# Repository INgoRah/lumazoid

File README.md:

# Lumazoid

Firmware for the Lumazoid realtime music visualizer board from nootropic design.
Detailed technical information about Lumazoid is at http://nootropicdesign.com/lumazoid

Install libraries/ffft in your Arduino sketchbook libraries folder.

Requires the [Adafruit NeoPixel library](https://github.com/adafruit/Adafruit_NeoPixel).

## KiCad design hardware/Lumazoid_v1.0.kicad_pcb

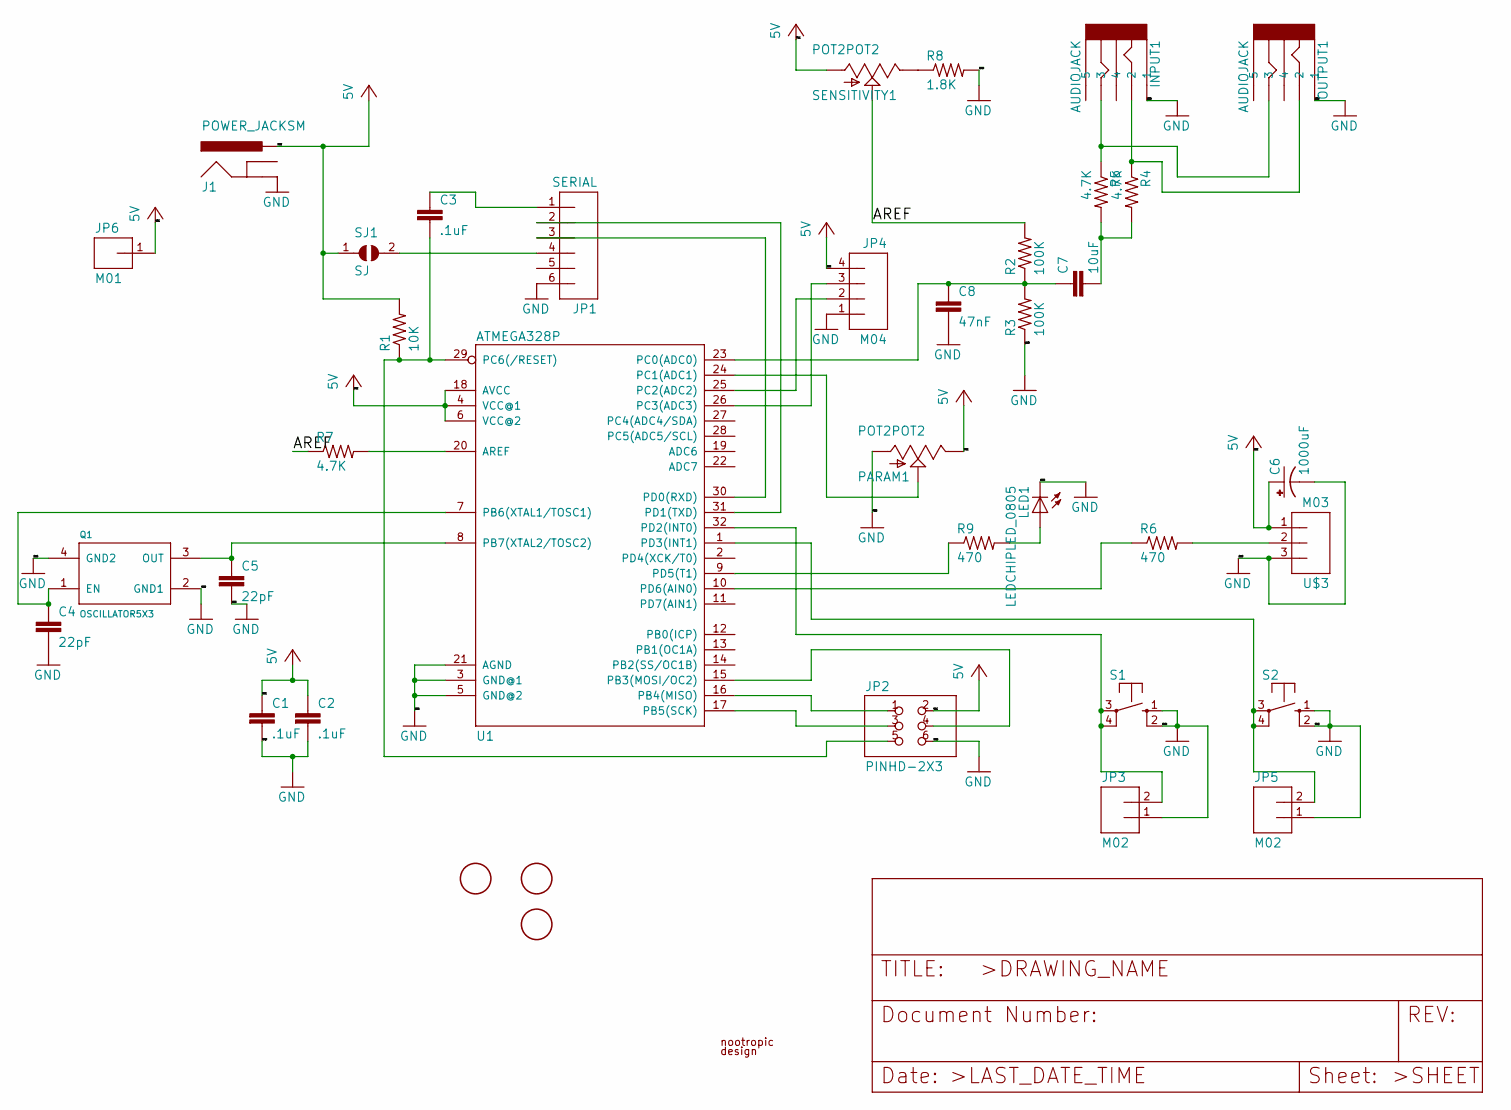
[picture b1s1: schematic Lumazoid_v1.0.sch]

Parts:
C1, C2, C3: .1uF; C0603
C4, C5: 22pF; C0603
C6: 1000uF; E5-10,5
C7: 10uF; C1206
C8: 47nF; C0603
FID1, FID2, FID3: FIDUCIAL; FIDUCIAL_1MM
INPUT1: AUDIOJACK
J1: POWER_JACKSM; POWER_JACK_SM
JP1: SERIAL; 1X06
JP2: PINHD-2X3; 2X03
JP3, JP5: M02; 1X02
JP4: M04; 1X04
JP6: M01; 1X01
LED1: LEDCHIPLED_0805; CHIPLED_0805
OUTPUT1: AUDIOJACK
PARAM1: POT2POT2; ALPS_POT
Q1: OSCILLATOR5X3; CRYSTAL-SMD-5X3
R1: 10K; R0603
R2, R3: 100K; R0603
R4, R5, R7: 4.7K; R0603
R6, R9: 470; R0603
R8: 1.8K; R0603
S1, S2: SWITCH-TACT6MMSMT-J; DTSM-6-JBEND
SENSITIVITY1: POT2POT2; ALPS_POT
SJ1: SJ
U1: ATMEGA328P; TQFP32-08
U$1: LOGO; LOGO_SMALL
U$3: M03; 1X03

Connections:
/AREF: R2.2, R7.1, SENSITIVITY1.P$2 (2)
GND: C1.2, C2.2, C4.2, C5.2, C6.-, C8.2, INPUT1.1, J1.GND, JP1.6, JP2.6, JP3.1, JP4.1, JP5.1, LED1.C, OUTPUT1.1, PARAM1.P$1 (1), Q1.2 (GND1), Q1.4 (GND2), R3.1, R8.2, S1.1 (S), S1.2 (S1), S2.1 (S), S2.2 (S1), U1.3 (GND@1), U1.5 (GND@2), U1.21 (AGND), U$3.3 (4)
unnamed: C3.1, JP1.1
unnamed: C3.2, JP2.5, R1.1, U1.29 (PC6(/RESET))
unnamed: C4.1, Q1.1 (EN), U1.7 (PB6(XTAL1/TOSC1))
unnamed: C5.1, Q1.3 (OUT), U1.8 (PB7(XTAL2/TOSC2))
unnamed: C7.1, C8.1, R2.1, R3.2, U1.23 (PC0(ADC0))
unnamed: C7.2, R4.2, R5.2
unnamed: INPUT1.2, OUTPUT1.2, R4.1
unnamed: INPUT1.3, OUTPUT1.3, R5.1
unnamed: JP1.2, U1.31 (PD1(TXD))
unnamed: JP1.3, U1.30 (PD0(RXD))
unnamed: JP1.4, SJ1.2
unnamed: JP2.1, U1.16 (PB4(MISO))
unnamed: JP2.3, U1.17 (PB5(SCK))
unnamed: JP2.4, U1.15 (PB3(MOSI/OC2))
unnamed: JP3.2, S1.3, S1.4 (P1), U1.32 (PD2(INT0))
unnamed: JP4.2, U1.25 (PC2(ADC2))
unnamed: JP4.3, U1.26 (PC3(ADC3))
unnamed: JP5.2, S2.3, S2.4 (P1), U1.1 (PD3(INT1))
unnamed: LED1.A, R9.2
unnamed: PARAM1.P$2 (2), U1.24 (PC1(ADC1))
unnamed: R6.1, U1.10 (PD6(AIN0))
unnamed: R6.2, U$3.2 (3)
unnamed: R7.2, U1.20 (AREF)
unnamed: R8.1, SENSITIVITY1.P$3 (3)
unnamed: R9.1, U1.9 (PD5(T1))
VCC: C1.1, C2.1, C6.+, J1.PWR, JP2.2, JP4.4, JP6.1, PARAM1.P$3 (3), R1.2, SENSITIVITY1.P$1 (1), SJ1.1, U1.4 (VCC@1), U1.6 (VCC@2), U1.18 (AVCC), U$3.1 (2)

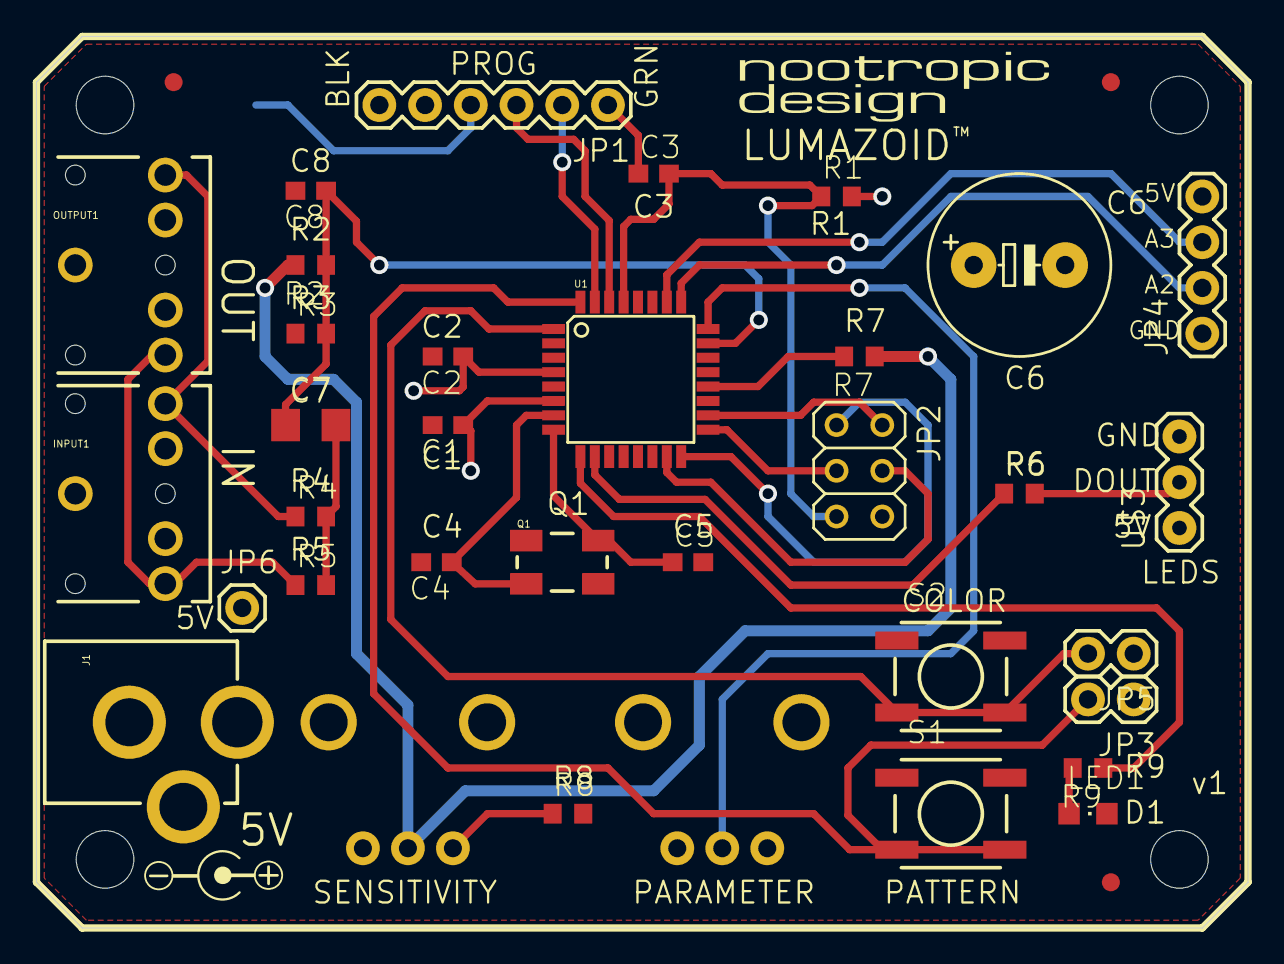
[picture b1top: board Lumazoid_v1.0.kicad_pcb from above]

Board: 2 copper layers, 67.3 x 49.5 mm, 43 parts (0 on the bottom side), 28 nets.

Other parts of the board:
@HOLE0, @HOLE1, @HOLE2, @HOLE3: (no value)

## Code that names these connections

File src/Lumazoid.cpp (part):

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#include <math.h>

//#define DEBUG
#define ADC_CHANNEL 0 /* ADC0 = PC0 = A0*/
#define N_BANDS 8
#define N_FRAMES 5
#define N_PEAKS 25
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#define LED_BRIGHTNESS 25
#define UNUSED 255

#define PATTERN_BUTTON_PIN 2 /* D2 = PD2 / INT0 */
#define COLOR_BUTTON_PIN 3 /* D3 = PD3 / INT1 */
#define LED_PIN 13 /* D13 = PB5, was D5 = PD5 */
#define LED_STRIP_PIN 6 /* D6 = PD6 */
#define PARM_POT 1

boolean EEPROMValid();
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
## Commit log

2021-12-20 Convert to PlatformIO and include KiCad files

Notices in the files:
src/Lumazoid.cpp:
Copyright (C) 2015 Michael Krumpus, nootropic design, LLC
This program is free software: you can redistribute it and/or modify
it under the terms of the GNU General Public License as published by
the Free Software Foundation, either version 3 of the License, or
(at your option) any later version.
